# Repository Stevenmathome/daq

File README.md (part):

# DAQ Rev B

Firmware for the Teensy 4.1 on the DAQ Rev B board. The operator interface is the panel: switches, a button, three 7-segment displays, and an E-stop on an L-shaped bracket, wired to the board's input and display headers. The other face of the bracket carries the connectors out to the stand. A laptop is optional. USB serial is a CSV log and a few commands, not a control GUI.

The pin numbers below were checked against the Rev B schematic and the Rev B v2 hardware. Digital inputs are not in DI-number order on pins 31–38, and the HX711 rate is set by solder jumpers. Both are called out in the pin map.

The KiCad project, fab files, and drawing set are in [hardware/](hardware/README.md).

## Safety

Valve gates are driven low before `setup()` does anything else, and again on every boot. HIGH turns a MOSFET on.

The hardware E-stop removes 12 V from the valve coils only. Q10, a P-FET in the valve 12 V rail, is driven by the normally-closed contact on J32 pins 1-2. Opening that contact turns the valve rail off. Logic and sensors stay powered, so sampling, the displays, and the CSV continue through a trip. The firmware does not drive Q10. It only watches the sense pin.

That sense is Teensy pin 10, through 1 kΩ and 100 nF, with a 10 kΩ pulldown on the board. HIGH means the E-stop is closed (OK). LOW means tripped, or the E-stop is unplugged. The latch then forces every valve gate off. The displays blink `STOP` while the line is still low, and blink `RST` after it goes high again, until the configured reset input. Reset is ignored while the sense is still low, including a reset that was already held. Press it again after release.

With no E-stop fitted, J32 pins 1-2 need a jumper. Otherwise Q10 keeps the valve rail off and the valves stay unpowered. The sense pin also reads low until something holds it high, so the firmware latch stays set too.

Arm is a permissive. A valve listed under `interlocks` stays off unless that arm input is active. Dropping arm clears a toggle, so re-arming does not turn the valve back on. A momentary output comes back only if the button is still held. The E-stop latch overrides arm.

Opening the USB serial port reboots a Teensy. The reboot drops the valves. Connect the logger before a run, not during one.

## Edit the configuration

`firmware/config.yaml` is the file the build uses, and it is the worked example. Change it in place, or keep a copy beside it and point the build at it by replacing that file.

A PlatformIO pre-build step runs `firmware/scripts/gen_config.py`, checks the file, and writes `firmware/include/config_gen.h`. The Teensy never parses YAML. Do not edit the header.

Check it without compiling:

```bash
cd firmware
python3 -m pip install -r requirements.txt
python3 scripts/gen_config.py config.yaml include/config_gen.h
```

Errors name the key. The build stops on the first failed check and prints every problem it found, not just the first.

What you set:

| Block | What it does |
|---|---|
| `load_cells` | Name, unit, `slope`, and `offset`. Raw is HX711 counts. Optional `points` table. |
| `pressures` | Same line. Raw is sensor volts, before the 10k/20k divider. |
| `thermocouples` | MAX31856 type, plus a correction line. Raw is the chip's degC. `slope: 1` and `offset: 0` leave it unchanged. |
| `pages` | Each page is the three channels the displays show, display 1 then 2 then 3. The page input cycles the list. |
| `inputs` | DI1–DI8, each exactly once. `action` is `arm`, `reset`, `toggle_valve`, `momentary_valve`, `tare`, `display_page`, or `none`. |
| `estop` | Sense GPIO, `active`, `pull`, and which input is the reset button. |
| `interlocks` | `valve` N requires an input whose action is `arm`. |

A toggle already ON when the board boots does not energize. Cycle it. That is deliberate: boot forces the valves off, and a toggle is an edge, not a level.

## How to calibrate

Every analog channel uses one line:

```text
value = slope * raw + offset
```

`raw` is not the same number for every kind of channel:

| Channel | raw |
|---|---|
| LC1–LC3 | HX711 counts |
| PT1–PT6 | volts at the sensor, before the 10k/20k divider |
| TC1–TC3 | the MAX31856 temperature in °C |

Two readings fix the line. `raw0` should read `value0`, `raw1` should read `value1`:

```text
slope  = (value1 - value0) / (raw1 - raw0)
offset = value0 - slope * raw0
```

A 0.5–4.5 V, 0–100 PSI transducer is that formula with the datasheet endpoints:

```text
slope  = (100 - 0) / (4.5 - 0.5) = 25
offset = 0 - 25 * 0.5 = -12.5
```

The example config already uses those numbers. ADC code 2730 is 2.2 V at the pin and 3.3 V at the sensor, which the line reads as 70 PSI.

A load cell is the same shape. Unloaded counts `Z`, counts `L` with a known weight `W`:

```text
slope  = W / (L - Z)
offset = -slope * Z
```

A negative slope flips a cell whose green and white wires are swapped.

An optional `points` list replaces the line when it is present. Each entry is `[raw, value]`. Two to eight points. Raw values must increase. Values must keep rising or keep falling, not both. Between points the firmware draws a straight segment. Outside the first and last point it extends that end segment.

Which numbers are actually used, per channel:

1. EEPROM, if `CAL SAVE` stored that channel. Boot prints `cal=eeprom`.
2. Otherwise `config.yaml`. Boot prints `cal=config`.
3. The tare button is applied after either of those. It is not saved. Reboot clears it. Boot never prints a tare source because tare starts at zero.

A bench session that has not been saved prints `cal=session` from `CAL SHOW` and from `INFO`. Reboot throws it away.

### Pressure from the datasheet

Nothing to do if the sensor is 0.5–4.5 V and 0–100 PSI. The example is already that line. For a 0–150 PSI sensor with the same voltages, set `slope: 37.5` and `offset: -18.75` (`150 / 4` and `-37.5 * 0.5`).

### Load cell on the bench

1. Open the serial port and wait until rows are printing. Opening the port reboots the board.
2. Unload the cell.
3. Send `CAL LC1 ZERO`. The current counts become the zero. Slope stays whatever the file (or EEPROM) had.
4. Apply a known load, for example 50 lbf.
5. Send `CAL LC1 SPAN 50`.
6. Send `CAL SHOW`. The LC1 block is YAML you can paste over that cell in `config.yaml`.
7. Send `CAL SAVE` if this board should keep the line across reboots without editing the file.

`CAL LC1 SPAN` without a `ZERO` in this session uses the raw where the current line already reads zero. On the example config that raw is 0, which is not an unloaded cell. Zero it first.

### Several points instead of one line

1. `CAL CLEAR LC1` if you want to leave the old line behind. Clearing writes EEPROM, so the file's line is what remains.
2. At each known load, send `CAL LC1 POINT <value>`. The first point is stored and the line is still used. The second point turns the table on.
3. `CAL SHOW`, then `CAL SAVE` or paste the block into `config.yaml`.

A point that repeats a raw, or that makes the values fold back, is rejected and the previous table is kept.

### Thermocouple correction

Leave `slope: 1` and `offset: 0` unless the probe is off. An ice bath is `CAL TC1 ZERO` (this raw should read 0 °C). A second known temperature is `CAL TC1 SPAN 100`. The chip type is separate from this line. This board is type K.

### Tare

The tare button, and `TARE LC1` or `TARE ALL`, subtract the live reading so the cell shows zero. They do not change slope, offset, or points, and they do not touch EEPROM. Power cycle clears them. Use `CAL … ZERO` when the zero should survive a reboot.

`CAL CLEAR` drops every EEPROM override and reloads the file. `CAL CLEAR PT1` does that for one channel. Both write EEPROM immediately.

### E-stop sense

```yaml
estop:
  pin: 10
  active: low   # LOW = tripped or unplugged; HIGH = closed, OK
  pull: none    # the board already has the 10k pulldown
  reset: DI7
```

Pin 10 is the Rev B v2 sense input. The board puts 1 kΩ in series, 100 nF to ground, and 10 kΩ to ground, so the firmware pull is `none`. `active: low` matches the pin: HIGH is healthy. The check rejects a pull-up or pull-down on this pin, and it rejects `active: high`. Other free GPIOs are **14, 39, 40, and 41**.

A digital-input header can be the sense line only if that input's `action` is `none`. Those headers already have a 10k pulldown, so `pull` must be `none` or the firmware would fight the resistor.

With no E-stop fitted, jumper J32 pins 1-2, or the valve rail stays off and pin 10 reads low so the firmware latch stays set.

`reset` must name the one input whose action is `reset`. The example uses DI7, active high: a normally-open button to +3.3 V on that header.

## Build and upload

PlatformIO, board `teensy41`, Arduino framework. On a Mac:

```bash
python3 -m pip install -r firmware/requirements.txt
# PlatformIO CLI: https://platformio.org/install/cli
cd firmware
pytest tests
pio run -e teensy41
pio run -e teensy41 -t upload
```

The Teensy VIN–VUSB pad has to be cut (PJRC documents the pads on the back of the board). After the cut, USB does not power the Teensy. J16 needs 12 V for the board to run, including during upload. The E-stop does not belong in series with J16. Q10 already opens only the valve 12 V rail. Jumper J32 pins 1-2 when no E-stop is plugged in, or that rail stays off.

`pytest` covers the config checks, the pressure and load-cell math, the E-stop latch rules, and that the CSV column list in the firmware matches the generator.

## Serial log

The port is the Teensy USB serial device. Tools ask for 115200 baud; USB CDC ignores it. On macOS the device is `/dev/cu.usbmodem…`.

```bash
pio device monitor -b 115200
```

Connecting resets the board. The first lines are comments (`#`). Data rows follow at `stream_hz` (80 Hz in the example). SJ1–SJ3 ship bridged to +3.3 V, so the load cells convert at 80 samples/s. Cut those jumpers and bridge the GND side for 10 samples/s, and lower `stream_hz` to match or the log repeats each sample.

```
t_us,LC1,LC2,LC3,LC1_raw,LC2_raw,LC3_raw,PT1,PT2,PT3,PT4,PT5,PT6,PT1_counts,PT2_counts,PT3_counts,PT4_counts,PT5_counts,PT6_counts,TC1,TC2,TC3,tc_fault,valves,inputs,arm,estop_sense,estop_latch,page
```

| Column | Meaning |
|---|---|
| `t_us` | `micros()` since boot. It wraps. |
| `LC*` | Engineering units from the config. `nan` until that cell has produced a sample. |
| `LC*_raw` | Signed HX711 counts. |
| `PT*` | PSI from the config. |
| `PT*_counts` | 12-bit ADC code, 0–4095, 3.3 V full scale. |
| `TC*` | Degrees C. `nan` on a fault or before the first read. |
| `tc_fault` | Bit 0 TC1, bit 1 TC2, bit 2 TC3. |
| `valves` | Outputs actually driven. Bit 0 is valve 1. Zero while the E-stop latch is set. |
| `inputs` | Raw pin level, not the active-high/low setting. Bit 0 is DI1. 1 means the pin is HIGH. |
| `arm` | 1 when every input with action `arm` is in its active state. |
| `estop_sense` | 1 when the sense line is tripped. |
| `estop_latch` | 1 from the trip until a valid reset. |
| `page` | Display page index, starting at 0. |

`# ESTOP` is printed when the latch sets. `# RESET` is printed when it clears. Those lines are not CSV. `grep -v '^#'` keeps the rows.

Commands, one per line:

| Command | Effect |
|---|---|
| `PING` | `# PONG <ms>` |
| `INFO` | Banner, sense, latch, stream rate. |
| `HELP` | The command list. |
| `STREAM <0-100>` | Row rate. 0 pauses rows. Does not touch the valves. 80 matches the factory HX711 jumpers. |
| `VALVE <1-7> <0\|1>` | Same rules as a panel toggle: rejected while latched or disarmed. |
| `ALLOFF` | Clears every valve request. |
| `TARE <LC1\|LC2\|LC3\|ALL>` | Subtracts the live reading until reboot. Does not change slope, offset, or EEPROM. |
| `CAL <ch> ZERO` | Current raw reads 0. Keeps slope, drops any point table. Not saved until `CAL SAVE`. |
| `CAL <ch> SPAN <value>` | Current raw reads `<value>`. Builds slope and offset from the last `ZERO` (or from the line's existing zero). |
| `CAL <ch> POINT <value>` | Adds `[raw, value]`. Two or more points replace the line. |
| `CAL SHOW` | Prints YAML for the active calibration, with `source=config`, `eeprom`, or `session`. |
| `CAL SAVE` | Writes session changes, and channels already in EEPROM, to EEPROM. |
| `CAL CLEAR [ch]` | Drops EEPROM overrides and reloads `config.yaml`. |
| `PAGE` | Next display page. |
| `RESET` | Clears the E-stop latch only if the sense line is released. |

A rejected valve answers `# ERR estop latched` or `# ERR interlock valve N`.

## Pin map

Arduino pin numbers on the Teensy 4.1.

| Function | Connector | Teensy pin | Notes |
|---|---|---|---|
| LC1 DOUT | U3, J17 | 3 | HX711 data |
| LC2 DOUT | U4, J18 | 0 | |
| LC3 DOUT | U5, J19 | 1 | |
| LC shared SCK | U3–U5 | 2 | One clock for all three. Read them together. |
| Display 1 CLK / DIO | J29 | 4 / 5 | Header: 1 +5 V, 2 GND, 3 CLK, 4 DIO |
| Display 2 CLK / DIO | J30 | 6 / 7 | |
| Display 3 CLK / DIO | J31 | 8 / 9 | |
| TC MOSI / MISO / SCK | — | 11 / 12 / 13 | MAX31856. Pin 13 is also the onboard LED. |
| TC1 CS | U6, J20 | 23 | DRDY and FAULT are not wired. The firmware polls SPI. |
| TC2 CS | U7, J21 | 22 | |
| TC3 CS | U8, J22 | 21 | |
| PT1 … PT6 | J23 … J28 | 20, 19, 18, 17, 16, 15 | A6 … A1 |
| Valve 1 … 6 | J1 … J6 | 24 … 29 | Low-side AO3400A. HIGH = on. |
| Extra 12 V | J7 | 30 | Valve 7 in the config. |
| DI1 | J12 | 38 | Not pin 31. See below. |
| DI2 | J13 | 37 | |
| DI3 | J14 | 36 | |
| DI4 | J10 | 35 | |
| DI5 | J11 | 34 | |
| DI6 | J9 | 33 | |
| DI7 | J8 | 31 | |
| DI8 | J15 | 32 | |
| E-stop sense | J32 (power), pin 10 (sense) | 10 | 1 kΩ, 100 nF, 10 kΩ pulldown. HIGH = OK, LOW = tripped or unplugged. |
| Unused | — | 14, 39, 40, 41 | Not connected on Rev B v2. |

Checked against the schematic, and where it disagrees with the obvious guess:

- **HX711 RATE defaults to +3.3 V through SJ1–SJ3**, so U3–U5 run at 80 samples/s. Cut the +3.3 V bridge and solder the other side for 10 samples/s. RATE is not a Teensy pin. The firmware still clocks all three chips from pin 2 when DOUT falls, and the not-ready wait is long enough for the 10 sample/s jumper.
- **Digital inputs are not DI1 = pin 31 through DI8 = pin 38.** The schematic and the change report wire them as DI7, DI8, DI6, DI5, DI4, DI3, DI2, DI1 on pins 31–38. The table above is that wiring. The config talks about DI1–DI8, and the firmware maps those names onto these pins.
- **Valve pins 24–30 match** the original plan: valves 1–6, then the extra 12 V output.
- **Display CLK/DIO pairs are pins 4/5, 6/7, and 8/9.** The report's "4–9" is these three pairs, in that order.
- **Thermocouple terminals are T+ on pin 1 and T- on pin 2.** ANSI type K is yellow positive and red negative. The example config selects type K.
- **E-stop sense is Teensy pin 10** on Rev B v2. The valve-power contact is J32 pins 1-2, driving P-FET Q10. The firmware only senses pin 10.

## Wiring

Board power is J16: pin 1 +12 V, pin 2 GND. The 5 V rail is the R-78E5.0 buck. Teensy VIN is fed from that 5 V through Schottky D9. Cut the VIN–VUSB pad before USB and 12 V are both connected. After the cut, the board does not run from USB alone.

**E-stop.** J32 pins 1-2 are the normally-closed contact in the gate drive of Q10, the P-FET that feeds 12 V to the valves. The contact opens and Q10 drops that rail. J16 stays powered, so the Teensy and the sensors keep running. Pin 10 is only the sense: 1 kΩ from the switched node, 100 nF to ground, 10 kΩ pulldown. HIGH is closed and healthy. LOW is open, tripped, or unplugged. Do not feed pin 10 from 12 V or 5 V. With no E-stop plugged in, jumper J32 pins 1-2. Leave them open and the valves have no 12 V, and pin 10 stays low so the firmware latch stays set.

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
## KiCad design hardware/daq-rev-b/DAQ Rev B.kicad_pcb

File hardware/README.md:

# DAQ Rev B hardware

KiCad 9 project for the current DAQ Rev B board: a Teensy 4.1 data-acquisition and seven-valve controller. Three HX711 load cells, six pressure inputs, three MAX31856 thermocouples, eight panel inputs, three TM1637-style display headers, and a hardware E-stop that drops only the valve 12 V rail. F1 on the front edge is a user-replaceable ATO/ATC blade-fuse holder.

Open `daq-rev-b/DAQ Rev B.kicad_pro` in KiCad 9. The folder name has no spaces. The project files keep the name KiCad saved them with. Symbols and the Teensy footprint live in `daq-rev-b/lib/` and the library tables use `${KIPRJMOD}`, so the project opens from this directory without any extra libraries.

## Where things are

| Path | Contents |
|---|---|
| `daq-rev-b/DAQ Rev B.kicad_sch` | Schematic, including the drawing sheets |
| `daq-rev-b/DAQ Rev B.kicad_pcb` | PCB |
| `daq-rev-b/lib/` | Vendored symbols, the Teensy 4.1 footprint, and the F1 blade-fuse holder footprint and 3D model |
| `daq-rev-b/fab/DAQ_RevB_gerbers.zip` | Gerbers and drills for the board house |
| `daq-rev-b/fab/gerbers/` | The same Gerbers unpacked |
| `daq-rev-b/fab/DAQ_RevB_BOM_JLCPCB.csv` | JLCPCB BOM. The Teensy is not on it |
| `daq-rev-b/fab/DAQ_RevB_CPL_JLCPCB.csv` | JLCPCB pick-and-place |
| `daq-rev-b/fab/DAQ_RevB_BOM_full.csv` | BOM with manufacturer part numbers |
| `daq-rev-b/docs/DAQ_RevB_docs.pdf` | Eight-sheet drawing set, including the first-power checklist |
| `daq-rev-b/docs/DAQ_RevB_S02`–`S08` `.kicad_sch` | Drawing-sheet sources. The schematic links them |
| `daq-rev-b/docs/png/` | PNG previews of those sheets |
| `daq-rev-b/docs/DAQ_RevB_solenoid_research.md` | Solenoid current notes |
| `daq-rev-b/review/DAQ_RevB_report.md` | Design report |
| `daq-rev-b/review/DAQ_RevB_schematic.pdf` | Schematic PDF |
| `daq-rev-b/review/DAQ_RevB_render_*.png` | Top, bottom, and isometric renders |

## Ordering

- The Teensy 4.1 is hand-fitted. JLCPCB does not place it. Solder the two 1×24 sockets and plug the module in. Cut the VIN–VUSB pad on the back of the Teensy before USB and 12 V are connected together. After that cut, 12 V on J16 is required both to power the board and to program the Teensy. USB alone does not run it.
- Thermocouples are type K. Pin 1 is T+ (yellow) and pin 2 is T- (red).
- Display headers J29–J31 supply 5 V. Use a TM1637 module whose CLK and DIO are not pulled up to 5 V. Teensy 4.1 pins are 3.3 V only.
- Valve terminals J1–J7 take 0.5 mm² (20 AWG) maximum. Use ferrules.
- With no E-stop fitted, jumper J32 pins 1–2. Those pins are the normally-closed contact that turns on Q10, the P-FET in the valve 12 V rail. Leave them open and the valves stay unpowered. Pin 10, the sense input, also stays low, so the firmware holds the valve latch.
- Size the 12 V supply for 15 A or more. Each valve channel is up to 2 A, and all seven on is 14 A.
- F1 is a Littelfuse 178.6165.0002 ATO/ATC blade-fuse holder (LCSC C207061) on the front edge. The holder is on the JLCPCB BOM. The fuse is not: fit a standard 20 A ATO/ATC fuse after assembly. If it blows, pull it and replace it from the front edge. The fuse body stands about 20 mm off the board. If the board mounts components-down toward the L-bracket, use standoffs about 25 mm long so the fuse clears the bracket.

Check the JLCPCB placement preview before paying. Look at Q1–Q8 pin 1, U3–U8 pin 1, electrolytic polarity, diode cathodes, and the Phoenix terminal orientation.

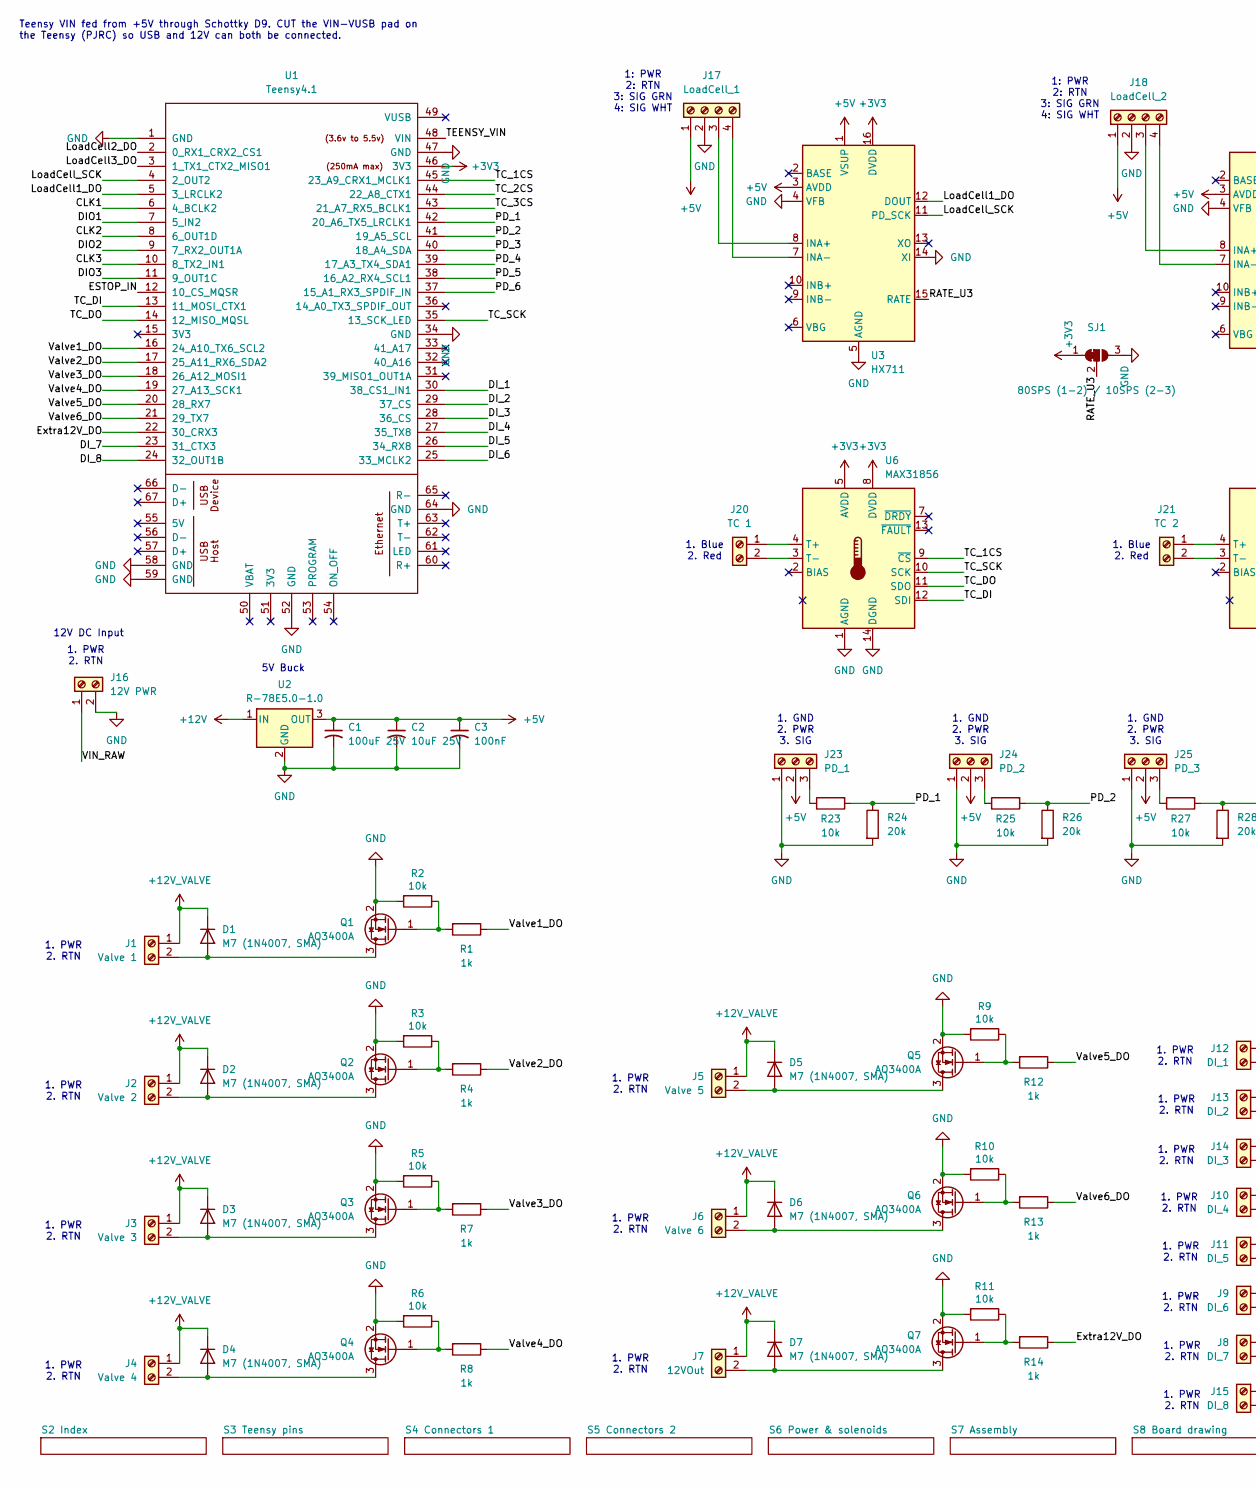
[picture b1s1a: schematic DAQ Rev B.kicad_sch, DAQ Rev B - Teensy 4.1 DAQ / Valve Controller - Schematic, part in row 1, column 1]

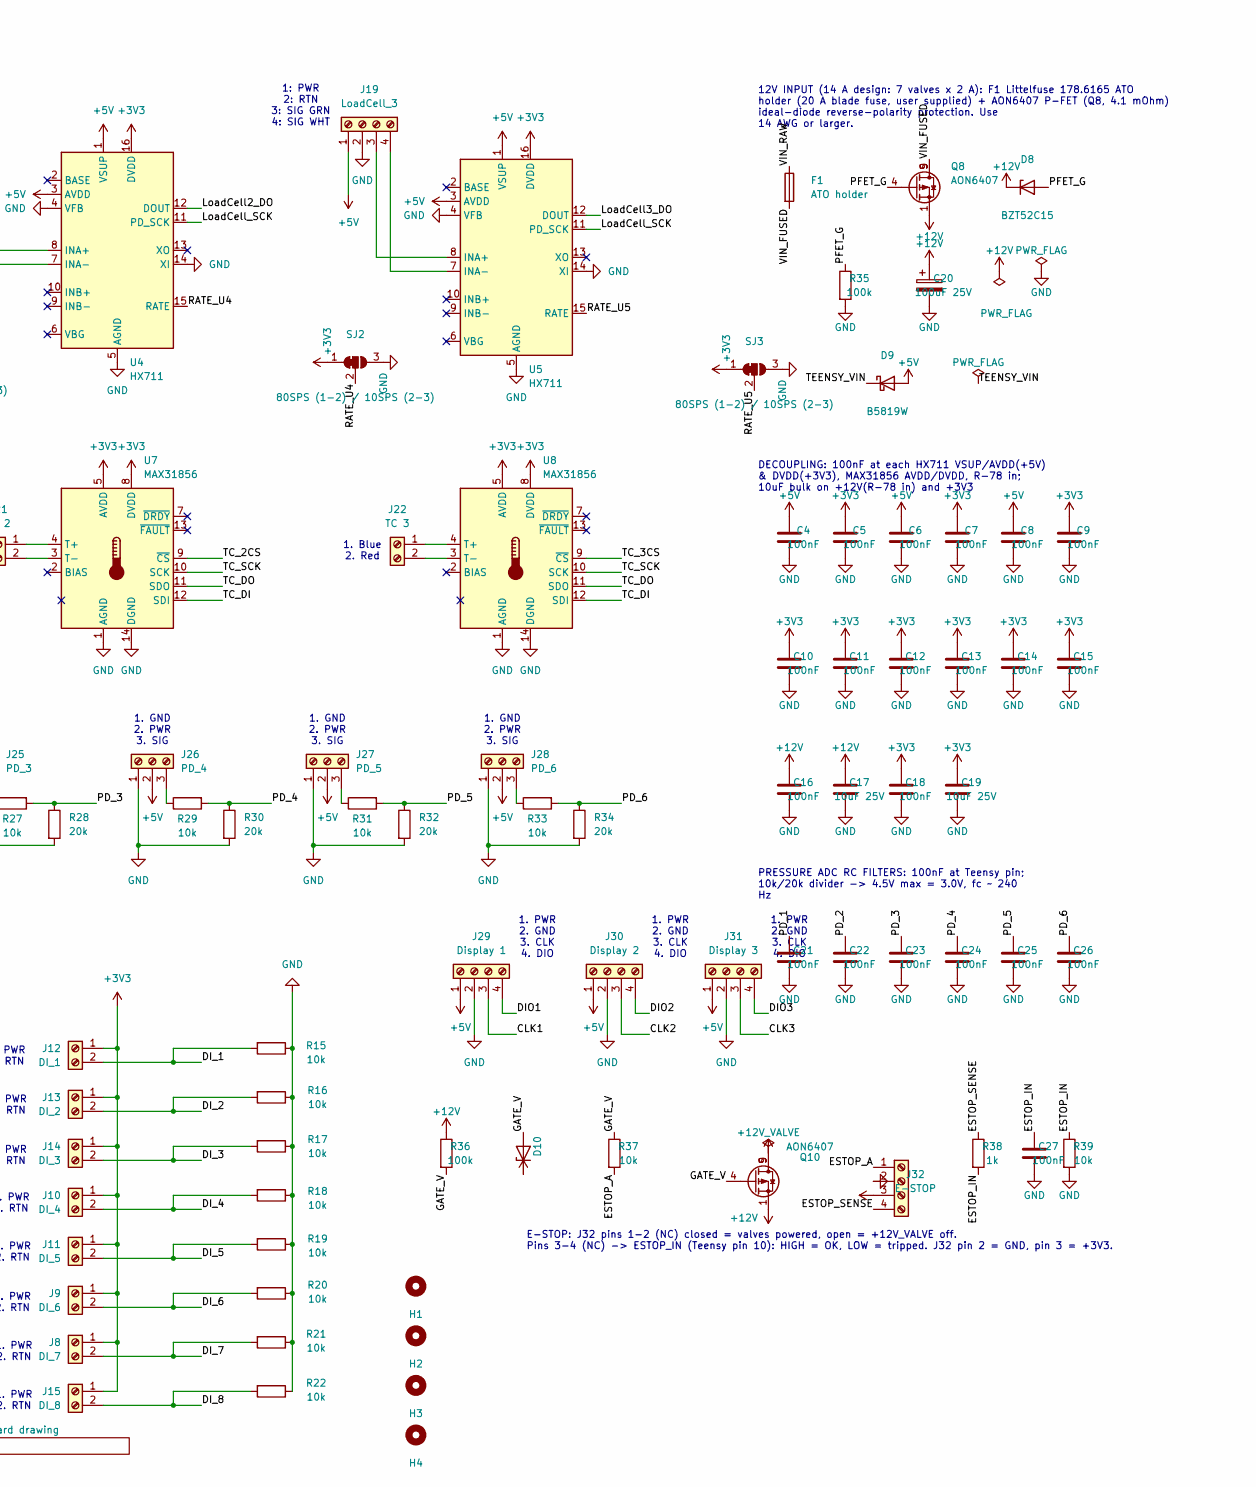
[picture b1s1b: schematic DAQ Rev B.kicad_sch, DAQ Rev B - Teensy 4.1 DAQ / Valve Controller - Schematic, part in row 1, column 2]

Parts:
C1, C20: 100uF 25V; CP_Elec_6.3x7.7; MPN RST100UF25V006; LCSC C4747965
C2, C17, C19: 10uF 25V; C_0805_2012Metric; MPN CL21A106KAYNNNE; LCSC C15850
C3, C4, C5, C6, C7, C8, C9, C10, C11, C12, C13, C14, C15, C16, C18, C21, C22, C23, C24, C25, C26, C27: 100nF; C_0603_1608Metric; MPN CC0603KRX7R9BB104; LCSC C14663
D1, D2, D3, D4, D5, D6, D7: M7 (1N4007, SMA); D_SMA; MPN M7; LCSC C95872
D8, D10: BZT52C15; D_SOD-123; MPN BZT52C15; LCSC C2104
D9: B5819W; D_SOD-123; MPN B5819W SL; LCSC C8598
F1: ATO holder; FuseHolder_Blade_ATO_Littelfuse_FLR_178.6165; MPN 178.6165.0002; LCSC C207061
H1, H2, H3, H4: MountingHole_M3; MountingHole_3.2mm_M3
J1: Valve 1; TerminalBlock_Phoenix_MPT-0,5-2-2.54_1x02_P2.54mm_Horizontal; MPN 1725656; LCSC C3029316
J2: Valve 2; TerminalBlock_Phoenix_MPT-0,5-2-2.54_1x02_P2.54mm_Horizontal; MPN 1725656; LCSC C3029316
J3: Valve 3; TerminalBlock_Phoenix_MPT-0,5-2-2.54_1x02_P2.54mm_Horizontal; MPN 1725656; LCSC C3029316
J4: Valve 4; TerminalBlock_Phoenix_MPT-0,5-2-2.54_1x02_P2.54mm_Horizontal; MPN 1725656; LCSC C3029316
J5: Valve 5; TerminalBlock_Phoenix_MPT-0,5-2-2.54_1x02_P2.54mm_Horizontal; MPN 1725656; LCSC C3029316
J6: Valve 6; TerminalBlock_Phoenix_MPT-0,5-2-2.54_1x02_P2.54mm_Horizontal; MPN 1725656; LCSC C3029316
J7: 12VOut; TerminalBlock_Phoenix_MPT-0,5-2-2.54_1x02_P2.54mm_Horizontal; MPN 1725656; LCSC C3029316
J8: DI_7; TerminalBlock_Phoenix_MPT-0,5-2-2.54_1x02_P2.54mm_Horizontal; MPN 1725656; LCSC C3029316
J9: DI_6; TerminalBlock_Phoenix_MPT-0,5-2-2.54_1x02_P2.54mm_Horizontal; MPN 1725656; LCSC C3029316
J10: DI_4; TerminalBlock_Phoenix_MPT-0,5-2-2.54_1x02_P2.54mm_Horizontal; MPN 1725656; LCSC C3029316
J11: DI_5; TerminalBlock_Phoenix_MPT-0,5-2-2.54_1x02_P2.54mm_Horizontal; MPN 1725656; LCSC C3029316
J12: DI_1; TerminalBlock_Phoenix_MPT-0,5-2-2.54_1x02_P2.54mm_Horizontal; MPN 1725656; LCSC C3029316
J13: DI_2; TerminalBlock_Phoenix_MPT-0,5-2-2.54_1x02_P2.54mm_Horizontal; MPN 1725656; LCSC C3029316
J14: DI_3; TerminalBlock_Phoenix_MPT-0,5-2-2.54_1x02_P2.54mm_Horizontal; MPN 1725656; LCSC C3029316
J15: DI_8; TerminalBlock_Phoenix_MPT-0,5-2-2.54_1x02_P2.54mm_Horizontal; MPN 1725656; LCSC C3029316
J16: 12V PWR; TerminalBlock_Phoenix_MKDS-1,5-2-5.08_1x02_P5.08mm_Horizont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; MPN KF128-5.08-2P-AA; LCSC C474952
J17: LoadCell_1; TerminalBlock_Phoenix_MPT-0,5-4-2.54_1x04_P2.54mm_Horizontal; MPN 1725672; LCSC C3816889
J18: LoadCell_2; TerminalBlock_Phoenix_MPT-0,5-4-2.54_1x04_P2.54mm_Horizontal; MPN 1725672; LCSC C3816889
J19: LoadCell_3; TerminalBlock_Phoenix_MPT-0,5-4-2.54_1x04_P2.54mm_Horizontal; MPN 1725672; LCSC C3816889
J20: TC 1; TerminalBlock_Phoenix_MPT-0,5-2-2.54_1x02_P2.54mm_Horizontal; MPN 1725656; LCSC C3029316
J21: TC 2; TerminalBlock_Phoenix_MPT-0,5-2-2.54_1x02_P2.54mm_Horizontal; MPN 1725656; LCSC C3029316
J22: TC 3; TerminalBlock_Phoenix_MPT-0,5-2-2.54_1x02_P2.54mm_Horizontal; MPN 1725656; LCSC C3029316
J23: PD_1; TerminalBlock_Phoenix_MPT-0,5-3-2.54_1x03_P2.54mm_Horizontal; MPN 1725669; LCSC C5288763
J24: PD_2; TerminalBlock_Phoenix_MPT-0,5-3-2.54_1x03_P2.54mm_Horizontal; MPN 1725669; LCSC C5288763
J25: PD_3; TerminalBlock_Phoenix_MPT-0,5-3-2.54_1x03_P2.54mm_Horizontal; MPN 1725669; LCSC C5288763
J26: PD_4; TerminalBlock_Phoenix_MPT-0,5-3-2.54_1x03_P2.54mm_Horizontal; MPN 1725669; LCSC C5288763
J27: PD_5; TerminalBlock_Phoenix_MPT-0,5-3-2.54_1x03_P2.54mm_Horizontal; MPN 1725669; LCSC C5288763
J28: PD_6; TerminalBlock_Phoenix_MPT-0,5-3-2.54_1x03_P2.54mm_Horizontal; MPN 1725669; LCSC C5288763
J29: Display 1; TerminalBlock_Phoenix_MPT-0,5-4-2.54_1x04_P2.54mm_Horizontal; MPN 1725672; LCSC C3816889
J30: Display 2; TerminalBlock_Phoenix_MPT-0,5-4-2.54_1x04_P2.54mm_Horizontal; MPN 1725672; LCSC C3816889
J31: Display 3; TerminalBlock_Phoenix_MPT-0,5-4-2.54_1x04_P2.54mm_Horizontal; MPN 1725672; LCSC C3816889
J32: E-STOP; TerminalBlock_Phoenix_MPT-0,5-4-2.54_1x04_P2.54mm_Horizontal; MPN 1725672; LCSC C3816889
Q1, Q2, Q3, Q4, Q5, Q6, Q7: AO3400A; SOT-23; MPN AO3400A; LCSC C20917
Q8, Q10: AON6407; DFN-8-1EP_6x5mm_P1.27mm_EP4x4mm; MPN AON6407; LCSC C7603355
R1, R4, R7, R8, R12, R13, R14, R38: 1k; R_0603_1608Metric; MPN 0603WAF1001T5E; LCSC C21190
R2, R3, R5, R6, R9, R10, R11, R15, R16, R17, R18, R19, R20, R21, R22, R23, R25, R27, R29, R31, R33, R37, R39: 10k; R_0603_1608Metric; MPN 0603WAF1002T5E; LCSC C25804
R24, R26, R28, R30, R32, R34: 20k; R_0603_1608Metric; MPN 0603WAF2002T5E; LCSC C4184
R35, R36: 100k; R_0603_1608Metric; MPN 0603WAF1003T5E; LCSC C25803
SJ1, SJ2, SJ3: 80SPS (1-2) / 10SPS (2-3); SolderJumper-3_P1.3mm_Bridged12_RoundedPad1.0x1.5mm
U1: Teensy4.1; Teensy41; MPN Teensy 4.1 (PJRC) on 2x HC-PM254-8.5H-1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
U2: R-78E5.0-1.0; Converter_DCDC_RECOM_R-78E-0.5_THT; MPN R-78E5.0-1.0; LCSC C22371890
U3, U4, U5: HX711; SOIC-16_3.9x9.9mm_P1.27mm; MPN HX711; LCSC C43656
U6, U7, U8: MAX31856; TSSOP-14_4.4x5mm_P0.65mm; MPN MAX31856MUD+; LCSC C116632

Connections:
+3V3: C5.1, C7.1, C9.1, C10.1, C11.1, C12.1, C13.1, C14.1, C15.1, C18.1, C19.1, J8.1, J9.1, J10.1, J11.1, J12.1, J13.1, J14.1, J15.1, J32.3, SJ1.1 (A), SJ2.1 (A), SJ3.1 (A), U1.46 (3V3), U3.16 (DVDD), U4.16 (DVDD), U5.16 (DVDD), U6.5 (AVDD), U6.8 (DVDD), U7.5 (AVDD), U7.8 (DVDD), U8.5 (AVDD), U8.8 (DVDD)
+5V: C1.1, C2.1, C3.1, C4.1, C6.1, C8.1, D9.2 (A), J17.1, J18.1, J19.1, J23.2, J24.2, J25.2, J26.2, J27.2, J28.2, J29.1, J30.1, J31.1, U2.3 (OUT), U3.1 (VSUP), U3.3 (AVDD), U4.1 (VSUP), U4.3 (AVDD), U5.1 (VSUP), U5.3 (AVDD)
+12V: C16.1, C17.1, C20.1, D8.1 (K), D10.1 (K), Q8.1 (S), Q8.2 (S), Q8.3 (S), Q10.1 (S), Q10.2 (S), Q10.3 (S), R36.1, U2.1 (IN)
+12V_VALVE: D1.1 (K), D2.1 (K), D3.1 (K), D4.1 (K), D5.1 (K), D6.1 (K), D7.1 (K), J1.1, J2.1, J3.1, J4.1, J5.1, J6.1, J7.1, Q10.5 (D), Q10.6 (D), Q10.7 (D), Q10.8 (D), Q10.9 (D)
/CLK1: J29.3, U1.6 (4_BCLK2)
/CLK2: J30.3, U1.8 (6_OUT1D)
/CLK3: J31.3, U1.10 (8_TX2_IN1)
/DIO1: J29.4, U1.7 (5_IN2)
/DIO2: J30.4, U1.9 (7_RX2_OUT1A)
/DIO3: J31.4, U1.11 (9_OUT1C)
/DI_1: J12.2, R15.2, U1.30 (38_CS1_IN1)
/DI_2: J13.2, R16.2, U1.29 (37_CS)
/DI_3: J14.2, R17.2, U1.28 (36_CS)
/DI_4: J10.2, R18.2, U1.27 (35_TX8)
/DI_5: J11.2, R19.2, U1.26 (34_RX8)
/DI_6: J9.2, R20.2, U1.25 (33_MCLK2)
/DI_7: J8.2, R21.2, U1.23 (31_CTX3)
/DI_8: J15.2, R22.2, U1.24 (32_OUT1B)
/ESTOP_A: J32.1, R37.2
/ESTOP_IN: C27.1, R38.2, R39.1, U1.12 (10_CS_MQSR)
/ESTOP_SENSE: J32.4, R38.1
/Extra12V_DO: R14.1, U1.22 (30_CRX3)
/GATE_V: D10.2 (A), Q10.4 (G), R36.2, R37.1
/LoadCell1_DO: U1.5 (3_LRCLK2), U3.12 (DOUT)
/LoadCell2_DO: U1.2 (0_RX1_CRX2_CS1), U4.12 (DOUT)
/LoadCell3_DO: U1.3 (1_TX1_CTX2_MISO1), U5.12 (DOUT)
/LoadCell_SCK: U1.4 (2_OUT2), U3.11 (PD_SCK), U4.11 (PD_SCK), U5.11 (PD_SCK)
/PD_1: C21.1, R23.2, R24.1, U1.42 (20_A6_TX5_LRCLK1)
/PD_2: C22.1, R25.2, R26.1, U1.41 (19_A5_SCL)
/PD_3: C23.1, R27.2, R28.1, U1.40 (18_A4_SDA)
/PD_4: C24.1, R29.2, R30.1, U1.39 (17_A3_TX4_SDA1)
/PD_5: C25.1, R31.2, R32.1, U1.38 (16_A2_RX4_SCL1)
/PD_6: C26.1, R33.2, R34.1, U1.37 (15_A1_RX3_SPDIF_IN)
/PFET_G: D8.2 (A), Q8.4 (G), R35.1
/RATE_U3: SJ1.2 (C), U3.15 (RATE)
/RATE_U4: SJ2.2 (C), U4.15 (RATE)
/RATE_U5: SJ3.2 (C), U5.15 (RATE)
/TC_1CS: U1.45 (23_A9_CRX1_MCLK1), U6.9 (~CS)
/TC_2CS: U1.44 (22_A8_CTX1), U7.9 (~CS)
/TC_3CS: U1.43 (21_A7_RX5_BCLK1), U8.9 (~CS)
/TC_DI: U1.13 (11_MOSI_CTX1), U6.12 (SDI), U7.12 (SDI), U8.12 (SDI)
/TC_DO: U1.14 (12_MISO_MQSL), U6.11 (SDO), U7.11 (SDO), U8.11 (SDO)
/TC_SCK: U1.35 (13_SCK_LED), U6.10 (SCK), U7.10 (SCK), U8.10 (SCK)
/TEENSY_VIN: D9.1 (K), U1.48 (VIN)
/VIN_FUSED: F1.2, Q8.5 (D), Q8.6 (D), Q8.7 (D), Q8.8 (D), Q8.9 (D)
/VIN_RAW: F1.1, J16.1
/Valve1_DO: R1.1, U1.16 (24_A10_TX6_SCL2)
/Valve2_DO: R4.1, U1.17 (25_A11_RX6_SDA2)
/Valve3_DO: R7.1, U1.18 (26_A12_MOSI1)
/Valve4_DO: R8.1, U1.19 (27_A13_SCK1)
/Valve5_DO: R12.1, U1.20 (28_RX7)
/Valve6_DO: R13.1, U1.21 (29_TX7)
GND: C1.2, C2.2, C3.2, C4.2, C5.2, C6.2, C7.2, C8.2, C9.2, C10.2, C11.2, C12.2, C13.2, C14.2, C15.2, C16.2, C17.2, C18.2, C19.2, C20.2, C21.2, C22.2, C23.2, C24.2, C25.2, C26.2, C27.2, J16.2, J17.2, J18.2, J19.2, J23.1, J24.1, J25.1, J26.1, J27.1, J28.1, J29.2, J30.2, J31.2, J32.2, Q1.2 (S), Q2.2 (S), Q3.2 (S), Q4.2 (S), Q5.2 (S), Q6.2 (S), Q7.2 (S), R2.2, R3.2, R5.2, R6.2, R9.2, R10.2, R11.2, R15.1, R16.1, R17.1, R18.1, R19.1, R20.1, R21.1, R22.1, R24.2, R26.2, R28.2, R30.2, R32.2, R34.2, R35.2, R39.2, SJ1.3 (B), SJ2.3 (B), SJ3.3 (B), U1.1 (GND), U1.34 (GND), U1.47 (GND), U1.52 (GND), U1.58 (GND), U1.59 (GND), U1.64 (GND), U2.2 (GND), U3.4 (VFB), U3.5 (AGND), U3.14 (XI), U4.4 (VFB), U4.5 (AGND), U4.14 (XI), U5.4 (VFB), U5.5 (AGND), U5.14 (XI), U6.1 (AGND), U6.14 (DGND), U7.1 (AGND), U7.14 (DGND), U8.1 (AGND)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
unnamed: D1.2 (A), J1.2, Q1.3 (D)
unnamed: D2.2 (A), J2.2, Q2.3 (D)
unnamed: D3.2 (A), J3.2, Q3.3 (D)
unnamed: D4.2 (A), J4.2, Q4.3 (D)
unnamed: D5.2 (A), J5.2, Q5.3 (D)
unnamed: D6.2 (A), J6.2, Q6.3 (D)
unnamed: D7.2 (A), J7.2, Q7.3 (D)
unnamed: J17.3, U3.8 (INA+)
unnamed: J17.4, U3.7 (INA-)
unnamed: J18.3, U4.8 (INA+)
unnamed: J18.4, U4.7 (INA-)
unnamed: J19.3, U5.8 (INA+)
unnamed: J19.4, U5.7 (INA-)
unnamed: J20.1, U6.4 (T+)
unnamed: J20.2, U6.3 (T-)
unnamed: J21.1, U7.4 (T+)
unnamed: J21.2, U7.3 (T-)
unnamed: J22.1, U8.4 (T+)
unnamed: J22.2, U8.3 (T-)
unnamed: J23.3, R23.1
unnamed: J24.3, R25.1
unnamed: J25.3, R27.1
unnamed: J26.3, R29.1
unnamed: J27.3, R31.1
unnamed: J28.3, R33.1
unnamed: Q1.1 (G), R1.2, R2.1
unnamed: Q2.1 (G), R3.1, R4.2
unnamed: Q3.1 (G), R5.1, R7.2
unnamed: Q4.1 (G), R6.1, R8.2
unnamed: Q5.1 (G), R9.1, R12.2
unnamed: Q6.1 (G), R10.1, R13.2
unnamed: Q7.1 (G), R11.1, R14.2

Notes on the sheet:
1: PWR 2: RTN 3: SIG GRN 4: SIG WHT
1. PWR 2. RTN
1. PWR 2. GND 3. CLK 4. DIO
5V Buck
1. GND 2. PWR 3. SIG
1. PWR 2. RTN
1. Blue 2. Red
Teensy VIN fed from +5V through Schottky D9. CUT the VIN-VUSB pad on the Teensy (PJRC) so USB and 12V can both be connected.
12V DC Input
12V INPUT (14 A design: 7 valves x 2 A): F1 Littelfuse 178.6165 ATO holder (20 A blade fuse, user supplied) + AON6407 P-FET (Q8, 4.1 mOhm) ideal-diode reverse-polarity protection. Use 14 AWG or larger.
DECOUPLING: 100nF at each HX711 VSUP/AVDD(+5V) & DVDD(+3V3), MAX31856 AVDD/DVDD, R-78 in; 10uF bulk on +12V(R-78 in) and +3V3
PRESSURE ADC RC FILTERS: 100nF at Teensy pin; 10k/20k divider -> 4.5V max = 3.0V, fc ~ 240 Hz
E-STOP: J32 pins 1-2 (NC) closed = valves powered, open = +12V_VALVE off. Pins 3-4 (NC) -> ESTOP_IN (Teensy pin 10): HIGH = OK, LOW = tripped. J32 pin 2 = GND, pin 3 = +3V3.

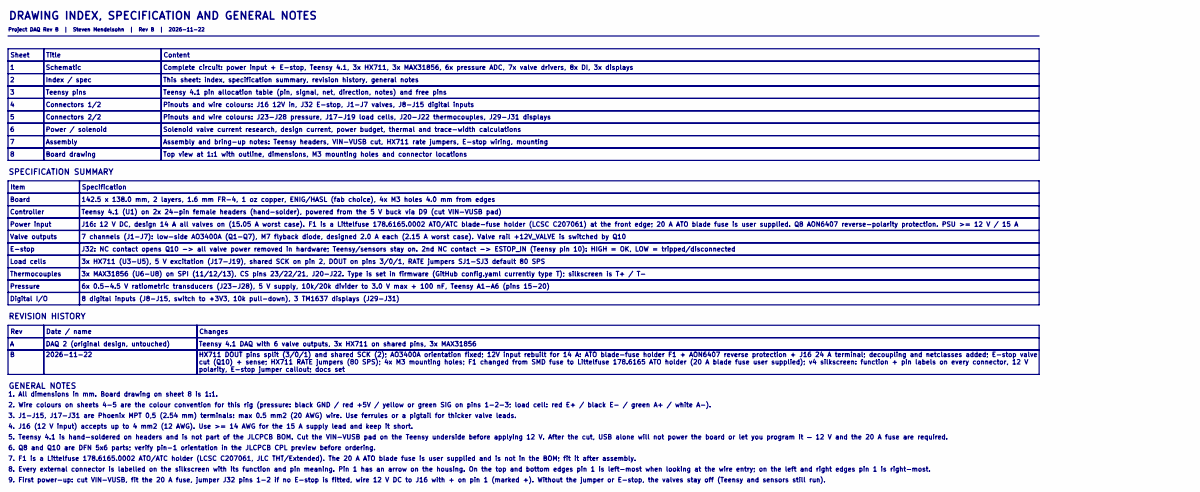
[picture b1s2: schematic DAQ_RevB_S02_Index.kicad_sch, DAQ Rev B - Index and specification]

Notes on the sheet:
DRAWING INDEX, SPECIFICATION AND GENERAL NOTES
Project DAQ Rev B | Steven Mendelsohn | Rev B | 2026-11-22
Sheet
Title
Content
Schematic
Complete circuit: power input + E-stop, Teensy 4.1, 3x HX711, 3x MAX31856, 6x pressure ADC, 7x valve drivers, 8x DI, 3x displays
Index / spec
This sheet: index, specification summary, revision history, general notes
Teensy pins
Teensy 4.1 pin allocation table (pin, signal, net, direction, notes) and free pins
Connectors 1/2
Pinouts and wire colours: J16 12V in, J32 E-stop, J1-J7 valves, J8-J15 digital inputs
Connectors 2/2
Pinouts and wire colours: J23-J28 pressure, J17-J19 load cells, J20-J22 thermocouples, J29-J31 displays
Power / solenoid
Solenoid valve current research, design current, power budget, thermal and trace-width calculations
Assembly
Assembly and bring-up notes: Teensy headers, VIN-VUSB cut, HX711 rate jumpers, E-stop wiring, mounting
Board drawing
Top view at 1:1 with outline, dimensions, M3 mounting holes and connector locations
SPECIFICATION SUMMARY
Item
Specification
Board
142.5 x 138.0 mm, 2 layers, 1.6 mm FR-4, 1 oz copper, ENIG/HASL (fab choice), 4x M3 holes 4.0 mm from edges
Controller
Teensy 4.1 (U1) on 2x 24-pin female headers (hand-solder), powered from the 5 V buck via D9 (cut VIN-VUSB pad)
Power input
J16: 12 V DC, design 14 A all valves on (15.05 A worst case). F1 is a Littelfuse 178.6165.0002 ATO/ATC blade-fuse holder (LCSC C207061) at the front edge; 20 A ATO blade fuse is user supplied. Q8 AON6407 reverse-polarity protection. PSU >= 12 V / 15 A
Valve outputs
7 channels (J1-J7): low-side AO3400A (Q1-Q7), M7 flyback diode, designed 2.0 A each (2.15 A worst case). Valve rail +12V_VALVE is switched by Q10
E-stop
J32: NC contact opens Q10 -> all valve power removed in hardware; Teensy/sensors stay on. 2nd NC contact -> ESTOP_IN (Teensy pin 10): HIGH = OK, LOW = tripped/disconnected
Load cells
3x HX711 (U3-U5), 5 V excitation (J17-J19), shared SCK on pin 2, DOUT on pins 3/0/1, RATE jumpers SJ1-SJ3 default 80 SPS
Thermocouples
3x MAX31856 (U6-U8) on SPI (11/12/13), CS pins 23/22/21, J20-J22. Type is set in firmware (GitHub config.yaml currently type T); silkscreen is T+ / T-
Pressure
6x 0.5-4.5 V ratiometric transducers (J23-J28), 5 V supply, 10k/20k divider to 3.0 V max + 100 nF, Teensy A1-A6 (pins 15-20)

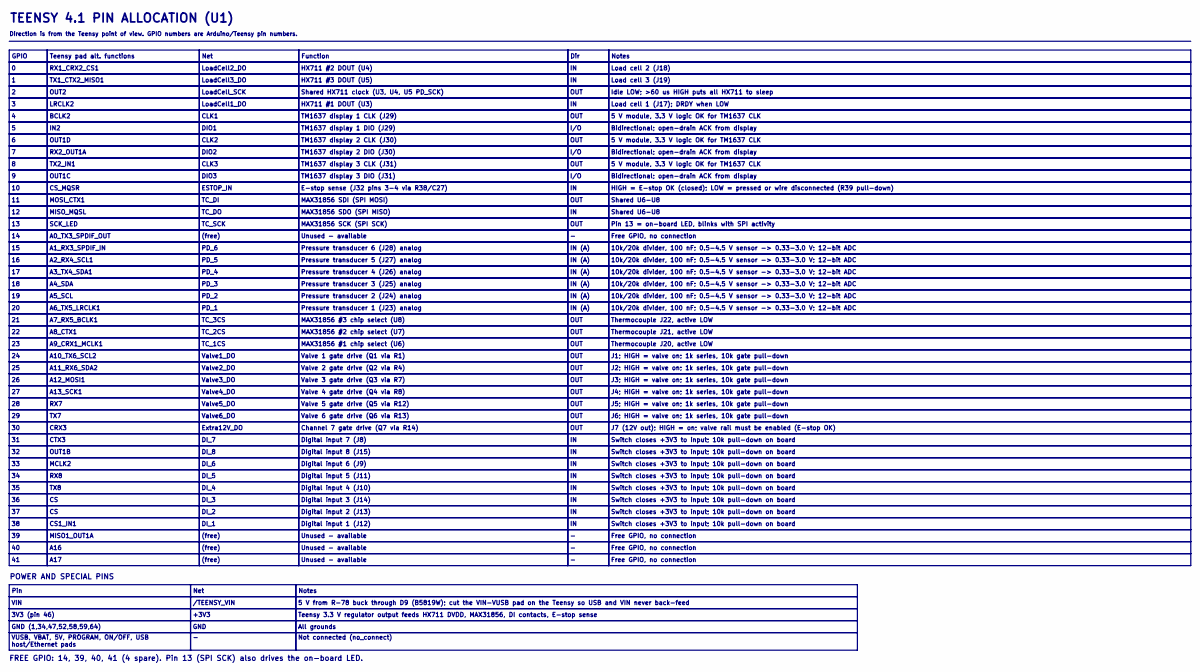
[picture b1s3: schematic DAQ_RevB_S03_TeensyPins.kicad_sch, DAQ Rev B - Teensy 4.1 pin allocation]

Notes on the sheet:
TEENSY 4.1 PIN ALLOCATION (U1)
Direction is from the Teensy point of view. GPIO numbers are Arduino/Teensy pin numbers.
GPIO
Teensy pad alt. functions
Net
Function
Dir
Notes
RX1_CRX2_CS1
LoadCell2_DO
HX711 #2 DOUT (U4)
Load cell 2 (J18)
TX1_CTX2_MISO1
LoadCell3_DO
HX711 #3 DOUT (U5)
Load cell 3 (J19)
OUT2
LoadCell_SCK
Shared HX711 clock (U3, U4, U5 PD_SCK)
OUT
Idle LOW; >60 us HIGH puts all HX711 to sleep
LRCLK2
LoadCell1_DO
HX711 #1 DOUT (U3)
Load cell 1 (J17); DRDY when LOW
BCLK2
CLK1
TM1637 display 1 CLK (J29)
5 V module, 3.3 V logic OK for TM1637 CLK
IN2
DIO1
TM1637 display 1 DIO (J29)
I/O
Bidirectional; open-drain ACK from display
OUT1D
CLK2
TM1637 display 2 CLK (J30)
RX2_OUT1A
DIO2
TM1637 display 2 DIO (J30)

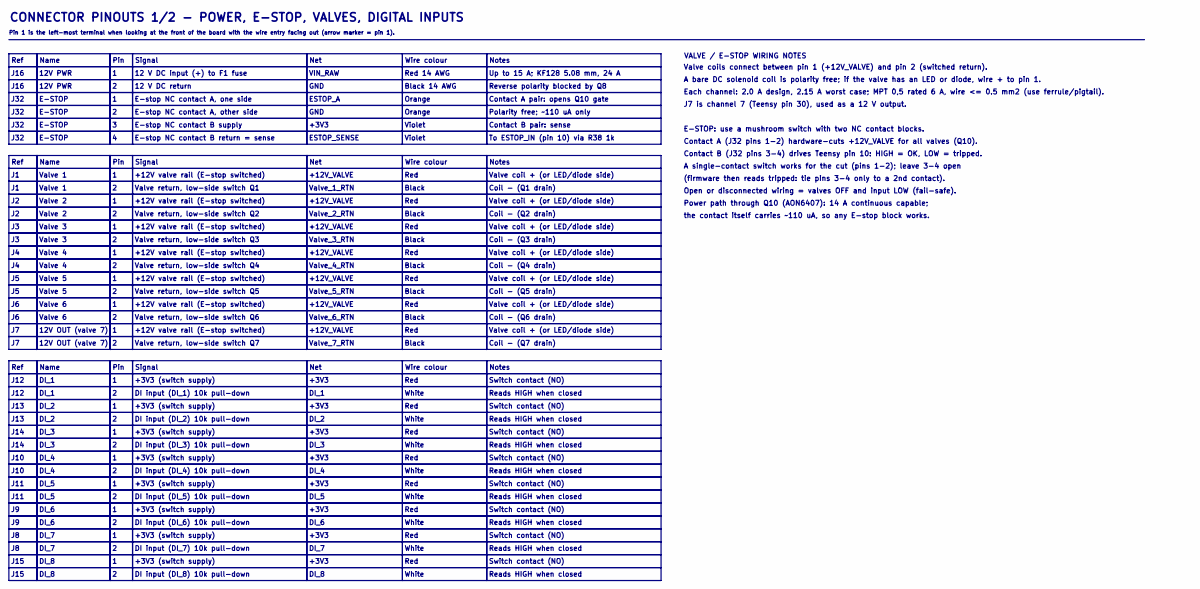
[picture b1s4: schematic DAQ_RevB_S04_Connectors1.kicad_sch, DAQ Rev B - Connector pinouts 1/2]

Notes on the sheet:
CONNECTOR PINOUTS 1/2 - POWER, E-STOP, VALVES, DIGITAL INPUTS
Pin 1 is the left-most terminal when looking at the front of the board with the wire entry facing out (arrow marker = pin 1).
Ref
Name
Pin
Signal
Net
Wire colour
Notes
J16
12V PWR
12 V DC input (+) to F1 fuse
VIN_RAW
Red 14 AWG
Up to 15 A; KF128 5.08 mm, 24 A
12 V DC return
GND
Black 14 AWG
Reverse polarity blocked by Q8
J32
E-STOP
E-stop NC contact A, one side
ESTOP_A
Orange
Contact A pair: opens Q10 gate
E-stop NC contact A, other side
Polarity free; ~110 uA only
E-stop NC contact B supply
+3V3
Violet
Contact B pair: sense
E-stop NC contact B return = sense
ESTOP_SENSE
To ESTOP_IN (pin 10) via R38 1k
Valve 1
+12V valve rail (E-stop switched)
+12V_VALVE
Red
Valve coil + (or LED/diode side)
Valve return, low-side switch Q1

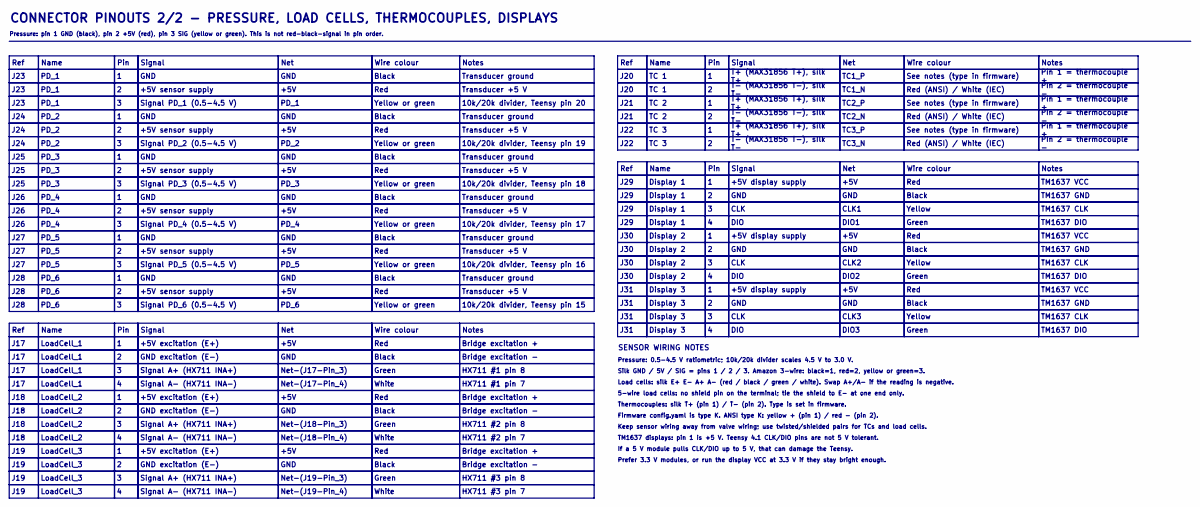
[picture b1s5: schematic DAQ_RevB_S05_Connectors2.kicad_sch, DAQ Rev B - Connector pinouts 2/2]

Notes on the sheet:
CONNECTOR PINOUTS 2/2 - PRESSURE, LOAD CELLS, THERMOCOUPLES, DISPLAYS
Pressure: pin 1 GND (black), pin 2 +5V (red), pin 3 SIG (yellow or green). This is not red-black-signal in pin order.
Ref
Name
Pin
Signal
Net
Wire colour
Notes
J23
PD_1
GND
Black
Transducer ground
+5V sensor supply
+5V
Red
Transducer +5 V
Signal PD_1 (0.5-4.5 V)
Yellow or green
10k/20k divider, Teensy pin 20
J24
PD_2
Signal PD_2 (0.5-4.5 V)
10k/20k divider, Teensy pin 19
J25
PD_3
Signal PD_3 (0.5-4.5 V)
10k/20k divider, Teensy pin 18
J26
PD_4
Signal PD_4 (0.5-4.5 V)
10k/20k divider, Teensy pin 17
J27
PD_5
Signal PD_5 (0.5-4.5 V)
10k/20k divider, Teensy pin 16
J28
PD_6
Signal PD_6 (0.5-4.5 V)

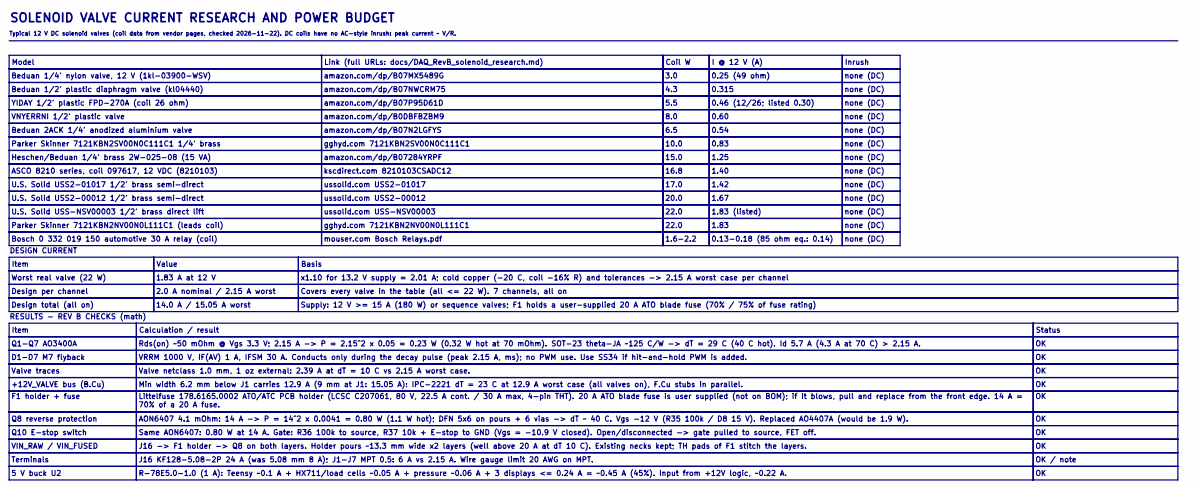
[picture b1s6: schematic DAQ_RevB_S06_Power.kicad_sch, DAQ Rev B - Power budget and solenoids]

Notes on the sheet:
SOLENOID VALVE CURRENT RESEARCH AND POWER BUDGET
Typical 12 V DC solenoid valves (coil data from vendor pages, checked 2026-11-22). DC coils have no AC-style inrush: peak current ~ V/R.
Model
Link (full URLs: docs/DAQ_RevB_solenoid_research.md)
Coil W
I @ 12 V (A)
Inrush
Beduan 1/4' nylon valve, 12 V (1kl-03900-WSV)
amazon.com/dp/B07MX5489G
3.0
0.25 (49 ohm)
none (DC)
Beduan 1/2' plastic diaphragm valve (kl04440)
amazon.com/dp/B07NWCRM75
4.3
0.315
YIDAY 1/2' plastic FPD-270A (coil 26 ohm)
amazon.com/dp/B07P95D61D
5.5
0.46 (12/26; listed 0.30)
VNYERRNI 1/2' plastic valve
amazon.com/dp/B0DBFBZBM9
8.0
0.60
Beduan 2ACK 1/4' anodized aluminium valve
amazon.com/dp/B07N2LGFYS
6.5
0.54
Parker Skinner 7121KBN2SV00N0C111C1 1/4' brass
gghyd.com 7121KBN2SV00N0C111C1
10.0
0.83
Heschen/Beduan 1/4' brass 2W-025-08 (15 VA)
amazon.com/dp/B07284YRPF
15.0
1.25
ASCO 8210 series, coil 097617, 12 VDC (8210103)
kscdirect.com 8210103CSADC12
16.8
1.40

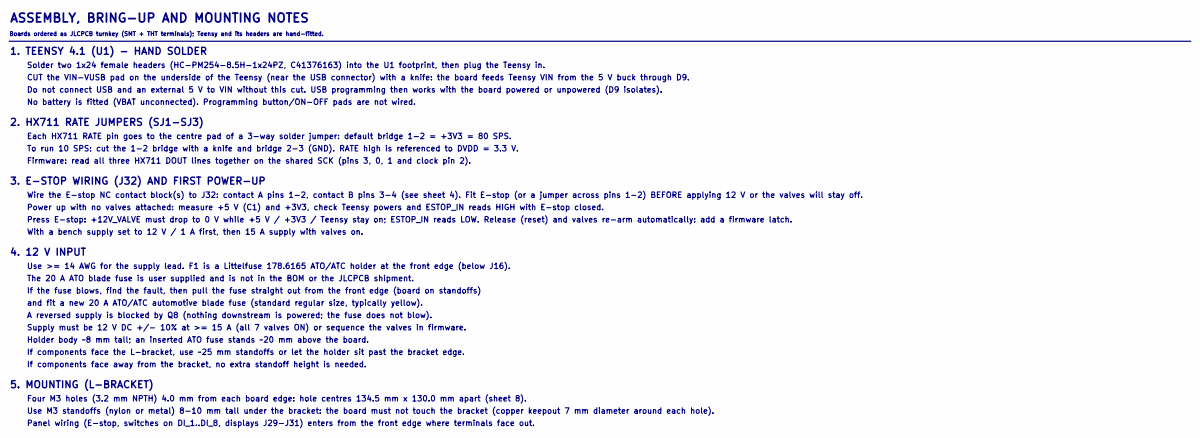
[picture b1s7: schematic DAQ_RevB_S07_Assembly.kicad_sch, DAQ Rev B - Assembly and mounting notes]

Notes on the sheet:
ASSEMBLY, BRING-UP AND MOUNTING NOTES
Boards ordered as JLCPCB turnkey (SMT + THT terminals); Teensy and its headers are hand-fitted.
1. TEENSY 4.1 (U1) - HAND SOLDER
Solder two 1x24 female headers (HC-PM254-8.5H-1x24PZ, C41376163) into the U1 footprint, then plug the Teensy in.
CUT the VIN-VUSB pad on the underside of the Teensy (near the USB connector) with a knife: the board feeds Teensy VIN from the 5 V buck through D9.
Do not connect USB and an external 5 V to VIN without this cut. USB programming then works with the board powered or unpowered (D9 isolates).
No battery is fitted (VBAT unconnected). Programming button/ON-OFF pads are not wired.
2. HX711 RATE JUMPERS (SJ1-SJ3)
Each HX711 RATE pin goes to the centre pad of a 3-way solder jumper: default bridge 1-2 = +3V3 = 80 SPS.
To run 10 SPS: cut the 1-2 bridge with a knife and bridge 2-3 (GND). RATE high is referenced to DVDD = 3.3 V.
Firmware: read all three HX711 DOUT lines together on the shared SCK (pins 3, 0, 1 and clock pin 2).
3. E-STOP WIRING (J32) AND FIRST POWER-UP
Wire the E-stop NC contact block(s) to J32: contact A pins 1-2, contact B pins 3-4 (see sheet 4). Fit E-stop (or a jumper across pins 1-2) BEFORE applying 12 V or the valves will stay off.
Power up with no valves attached: measure +5 V (C1) and +3V3, check Teensy powers and ESTOP_IN reads HIGH with E-stop closed.
Press E-stop: +12V_VALVE must drop to 0 V while +5 V / +3V3 / Teensy stay on; ESTOP_IN reads LOW. Release (reset) and valves re-arm automatically: add a firmware latch.
With a bench supply set to 12 V / 1 A first, then 15 A supply with valves on.
4. 12 V INPUT
Use >= 14 AWG for the supply lead. F1 is a Littelfuse 178.6165 ATO/ATC holder at the front edge (below J16).
The 20 A ATO blade fuse is user supplied and is not in the BOM or the JLCPCB shipment.
If the fuse blows, find the fault, then pull the fuse straight out from the front edge (board on standoffs)
and fit a new 20 A ATO/ATC automotive blade fuse (standard regular size, typically yellow).
A reversed supply is blocked by Q8 (nothing downstream is powered; the fuse does not blow).
Supply must be 12 V DC +/- 10% at >= 15 A (all 7 valves ON) or sequence the valves in firmware.
Holder body ~8 mm tall; an inserted ATO fuse stands ~20 mm above the board.
If components face the L-bracket, use ~25 mm standoffs or let the holder sit past the bracket edge.
If components face away from the bracket, no extra standoff height is needed.
5. MOUNTING (L-BRACKET)
Four M3 holes (3.2 mm NPTH) 4.0 mm from each board edge: hole centres 134.5 mm x 130.0 mm apart (sheet 8).
Use M3 standoffs (nylon or metal) 8-10 mm tall under the bracket: the board must not touch the bracket (copper keepout 7 mm diameter around each hole).
Panel wiring (E-stop, switches on DI_1..DI_8, displays J29-J31) enters from the front edge where terminals face out.
